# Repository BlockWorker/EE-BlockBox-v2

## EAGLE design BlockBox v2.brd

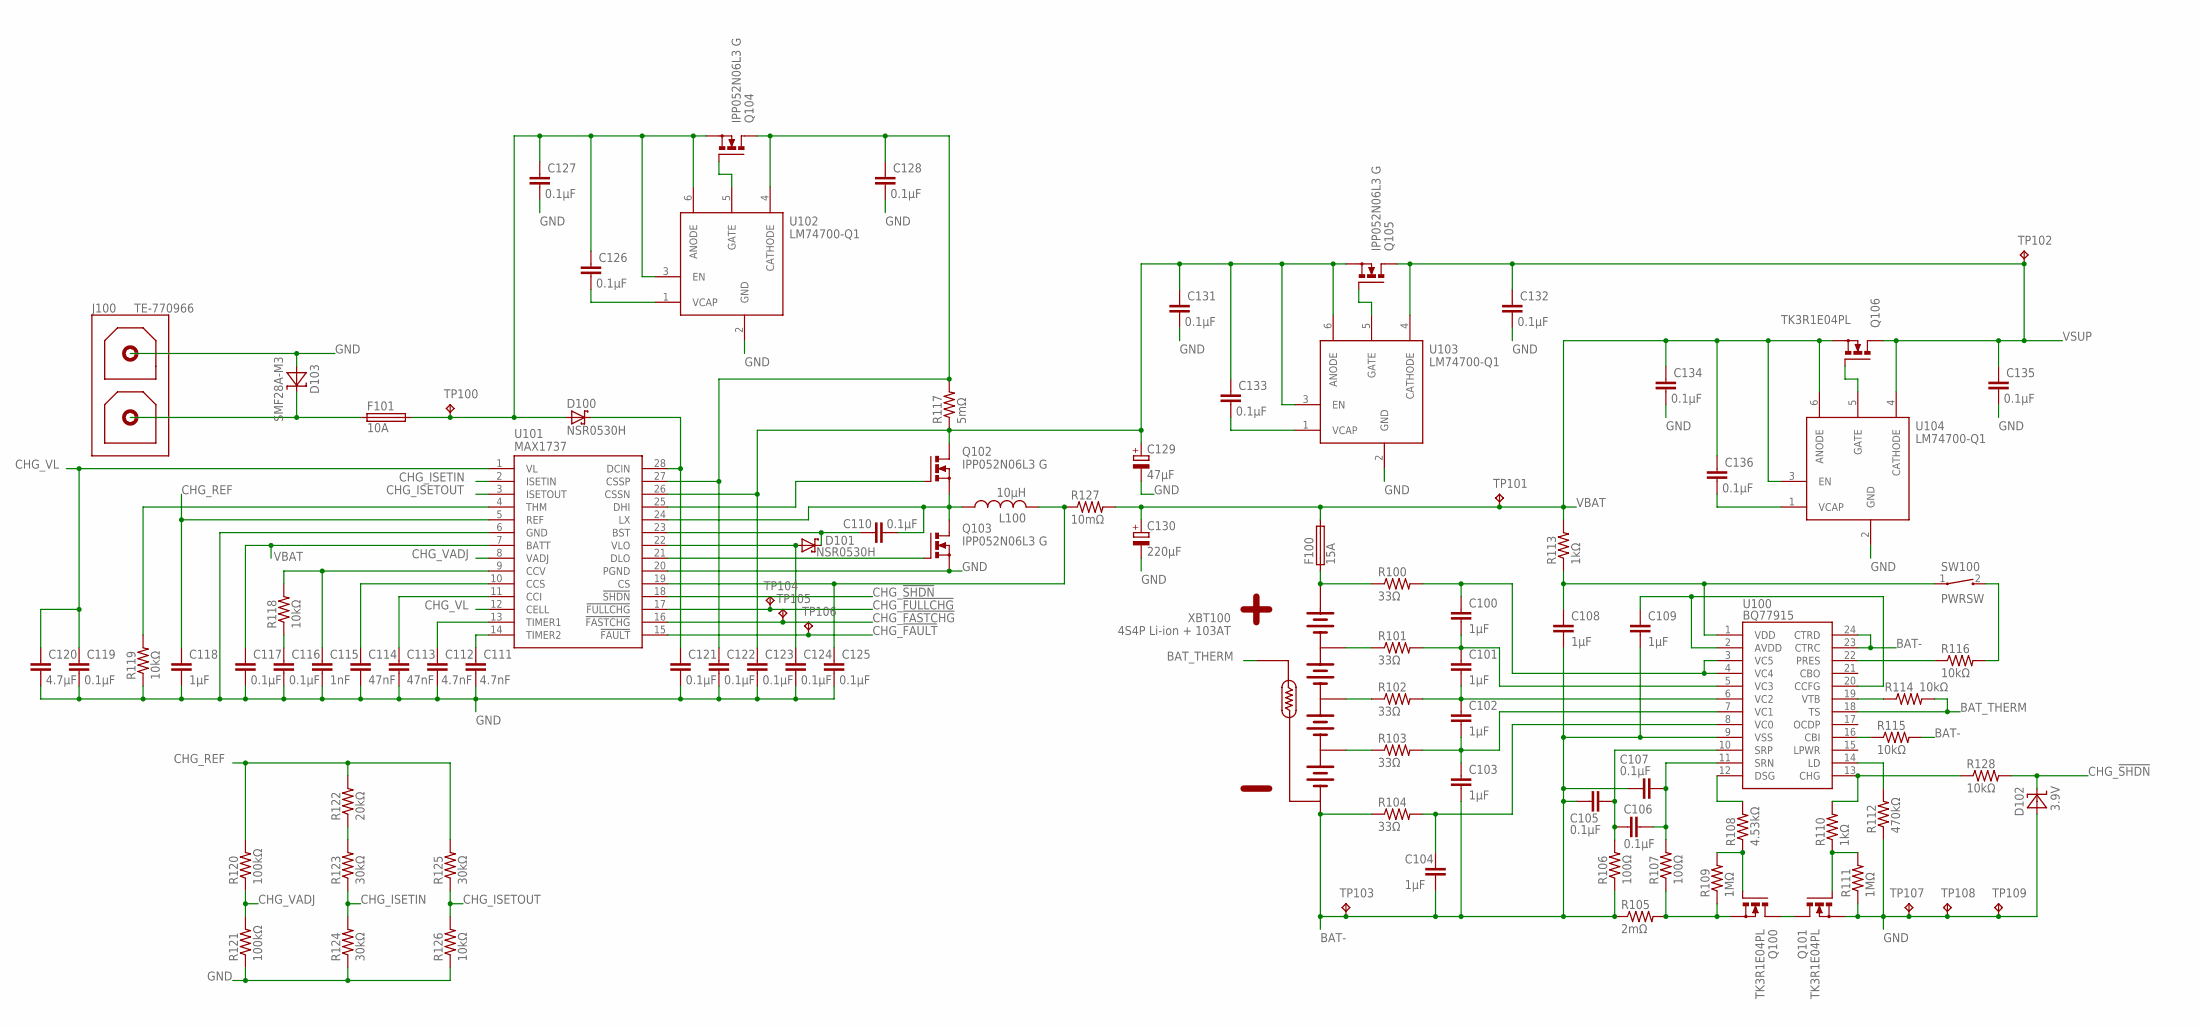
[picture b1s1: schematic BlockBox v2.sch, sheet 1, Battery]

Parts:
C100, C101, C102, C103, C104, C108, C109, C118: 1µF; C0603
C105, C106, C107, C110, C116, C117, C119, C121, C122, C123, C124, C125, C126, C127, C128, C131, C132, C133, C134, C135, C136: 0.1µF; C0603
C111, C112: 4.7nF; C0603
C113, C114: 47nF; C0603
C115: 1nF; C0603
C120: 4.7µF; C0805
C129: 47µF; E2,5-6
C130: 220µF; E3,5-8
D100, D101: NSR0530H; SOD323
D102: 3.9V; SOD323
D103: SMF28A-M3; DO-219AB
F100: 15A; F2410
F101: 10A; F2410
J100: TE-770966
L100: 10µH; PM5022
Q100, Q101, Q106: TK3R1E04PL; TO220BV-HS1
Q102, Q103, Q104, Q105: IPP052N06L3 G; TO220BV-HS1
R100, R101, R102, R103, R104: 33Ω; R0603
R105: 2mΩ; R2512
R106, R107: 100Ω; R0603
R108: 4.53kΩ; R0603
R109, R111: 1MΩ; R0603
R110, R113: 1kΩ; R0603
R112: 470kΩ; R0603
R114, R115, R116, R118, R119, R126, R128: 10kΩ; R0603
R117: 5mΩ; R1206
R120, R121: 100kΩ; R0603
R122: 20kΩ; R0603
R123, R124, R125: 30kΩ; R0603
R127: 10mΩ; R1206
SW100: PWRSW; WIRE-2P-SIMPLE
TP100, TP101, TP102, TP103, TP104, TP105, TP106, TP107, TP108, TP109: TPTP15R; TP15R
U100: BQ77915; TSSOP24
U101: MAX1737; QSOP28
U102, U103, U104: LM74700-Q1; SOT23-6L
XBT100: 4S4P Li-ion + 103AT; TE-770970

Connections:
BAT-: C103.2, C104.2, C105.1, C107.1, C108.2, C109.2, R104.1, R105.1, R106.1, R115.2, TP103.TP, U100.9 (VSS), U100.23 (CTRC), U100.24 (CTRD), XBT100.5 (-), XBT100.6 (-); also elsewhere on the board
BAT-_INT1: Q100.S, R105.2, R107.1, R109.1
BAT-_INT2: Q100.D, Q101.D
BAT_AVDD: C109.1, U100.2 (AVDD), U100.20 (CCFG)
BAT_BAL0: C104.1, R104.2, U100.8 (VC0)
BAT_BAL1: C102.2, C103.1, R103.2, U100.7 (VC1)
BAT_BAL2: C101.2, C102.1, R102.2, U100.6 (VC2)
BAT_BAL3: C100.2, C101.1, R101.2, U100.5 (VC3)
BAT_BAL4: C100.1, R100.2, U100.3 (VC5), U100.4 (VC4)
BAT_CBI: R115.1, U100.16 (CBI)
BAT_CHG_CTL: R110.2, R128.1, U100.13 (CHG)
BAT_CHG_GATE: Q101.G, R110.1, R111.2
BAT_CSN: C106.2, C107.2, R107.2, U100.11 (SRN); also elsewhere on the board
BAT_CSP: C105.2, C106.1, R106.2, U100.10 (SRP); also elsewhere on the board
BAT_DSG_CTL: R108.2, U100.12 (DSG)
BAT_DSG_GATE: Q100.G, R108.1, R109.2
BAT_INT1: R103.1, XBT100.4 (BAL1)
BAT_INT2: R102.1, XBT100.3 (BAL2)
BAT_INT3: R101.1, XBT100.7 (BAL3)
BAT_LD: R112.2, U100.14 (LD)
BAT_PRES: R116.1, U100.22 (PRES)
BAT_PRES_SW: R116.2, SW100.2
BAT_THERM: R114.2, U100.18 (TS), XBT100.8 (THERM1)
BAT_VDD: C108.1, R113.1, SW100.1, U100.1 (VDD)
BAT_VTB: R114.1, U100.19 (VTB)
CHG_!FASTCHG: TP105.TP, U101.16 (!FASTCHG); also elsewhere on the board
CHG_!FAULT: TP106.TP, U101.15 (!FAULT); also elsewhere on the board
CHG_!FULLCHG: TP104.TP, U101.17 (!FULLCHG); also elsewhere on the board
CHG_!SHDN: D102.1 (C), R128.2, U101.18 (!SHDN)
CHG_BST: C110.1, D101.1 (C), U101.23 (BST)
CHG_CCI: C113.1, U101.11 (CCI)
CHG_CCS: C114.1, U101.10 (CCS)
CHG_CCV: C115.1, R118.2, U101.9 (CCV)
CHG_CCV_FILT: C116.1, R118.1
CHG_CS: C125.1, L100.2, R127.1, U101.19 (CS)
CHG_CSSN: C123.1, C129.+, C131.1, C133.1, Q102.D, Q105.S, R117.1, U101.26 (CSSN), U103.3 (EN), U103.6 (ANODE)
CHG_CSSP: C122.1, C128.1, Q104.D, R117.2, U101.27 (CSSP), U102.4 (CATHODE)
CHG_DCIN: C121.1, D100.1 (C), U101.28 (DCIN)
CHG_DHI: Q102.G, U101.25 (DHI)
CHG_DLO: Q103.G, U101.21 (DLO)
CHG_ISETIN: R123.1, R124.2, U101.2 (ISETIN)
CHG_ISETIN_INT: R122.1, R123.2
CHG_ISETOUT: R125.1, R126.2, U101.3 (ISETOUT)
CHG_LX: C110.2, L100.1, Q102.S, Q103.D, U101.24 (LX)
CHG_REF: C118.1, R120.2, R122.2, R125.2, U101.5 (REF)
CHG_THM: R119.2, U101.4 (THM)
CHG_TIMER1: C112.1, U101.13 (TIMER1)
CHG_TIMER2: C111.1, U101.14 (TIMER2)
CHG_VADJ: R120.1, R121.2, U101.8 (VADJ)
CHG_VL: C119.1, C120.1, U101.1 (VL), U101.12 (CELL)
CHG_VLO: C124.1, D101.2 (A), U101.22 (VLO)
GND: C111.2, C112.2, C113.2, C114.2, C115.2, C116.2, C117.2, C118.2, C119.2, C120.2, C121.2, C122.2, C123.2, C124.2, C125.2, C127.2, C128.2, C129.-, C130.-, C131.2, C132.2, C134.2, C135.2, D102.2 (A), D103.A, J100.2, Q101.S, Q103.S, R111.1, R112.1, R119.1, R121.1, R124.1, R126.1, TP107.TP, TP108.TP, TP109.TP, U101.6 (GND), U101.20 (PGND), U102.2 (GND), U103.2 (GND), U104.2 (GND); also elsewhere on the board
VBAT: C117.1, C130.+, C134.1, C136.1, F100.2, Q106.S, R113.2, R127.2, TP101.TP, U101.7 (BATT), U104.3 (EN), U104.6 (ANODE); also elsewhere on the board
VBAT_PREFUSE: F100.1, R100.1, XBT100.1 (+), XBT100.2 (+)
VIN_EXT: D103.K (C), F101.1, J100.1
VIN_EXT_FUSED: C126.1, C127.1, D100.2 (A), F101.2, Q104.S, TP100.TP, U102.3 (EN), U102.6 (ANODE)
VIN_ID_GATE: Q104.G, U102.5 (GATE)
VIN_ID_VCAP: C126.2, U102.1 (VCAP)
VSUP: C132.1, C135.1, Q105.D, Q106.D, TP102.TP, U103.4 (CATHODE), U104.4 (CATHODE); also elsewhere on the board
VSUP_ID1_GATE: Q105.G, U103.5 (GATE)
VSUP_ID1_VCAP: C133.2, U103.1 (VCAP)
VSUP_ID2_GATE: Q106.G, U104.5 (GATE)
VSUP_ID2_VCAP: C136.2, U104.1 (VCAP)

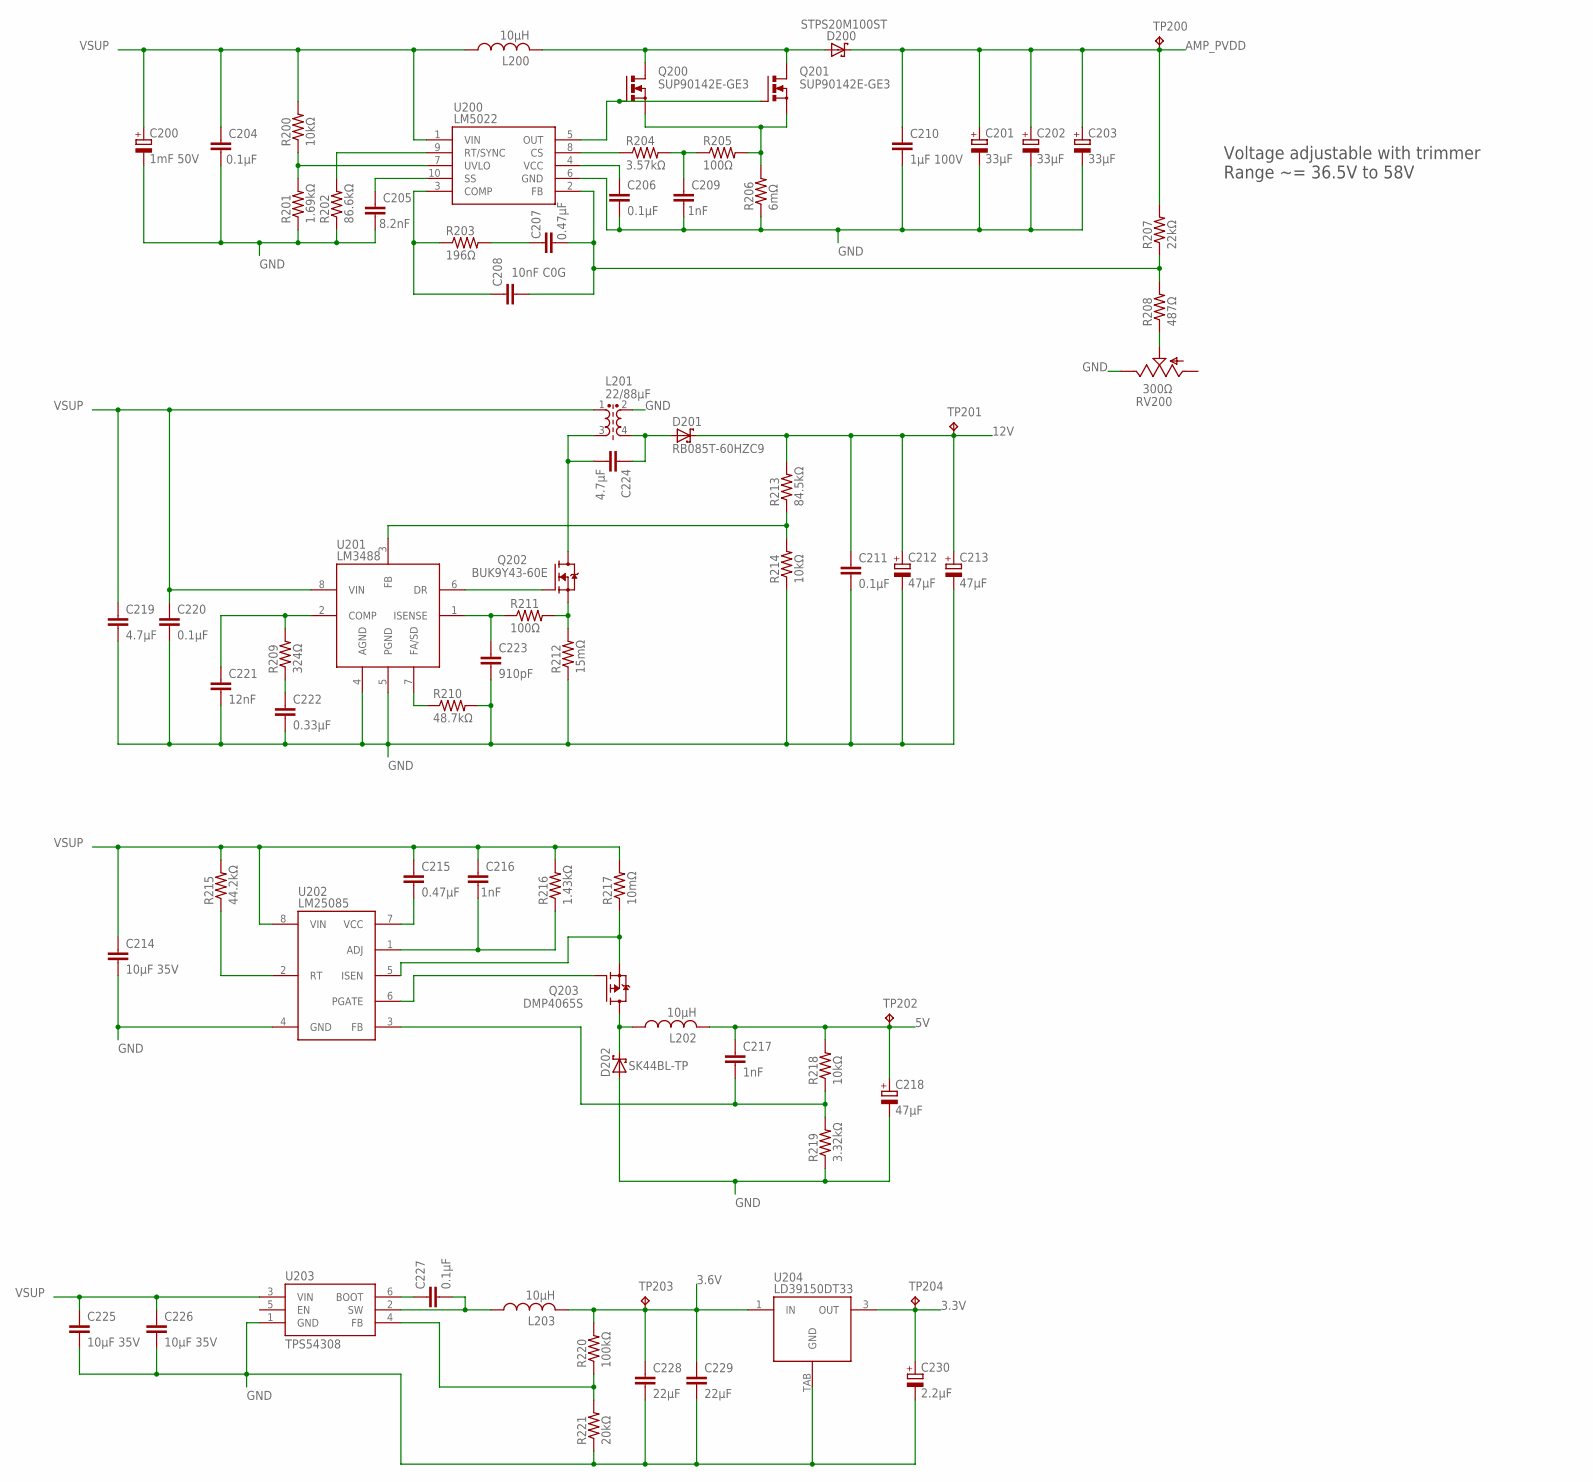
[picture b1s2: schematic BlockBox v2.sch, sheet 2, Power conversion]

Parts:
C200: 1mF 50V; E7,5-16
C201, C202, C203: 33µF; E3,5-8
C204, C206, C211, C220, C227: 0.1µF; C0603
C205: 8.2nF; C0603
C207: 0.47µF; C050-035X075
C208: 10nF C0G; C0603
C209, C216, C217: 1nF; C0603
C210: 1µF 100V; C1206
C212, C213, C218: 47µF; E2,5-6
C214, C225, C226: 10µF 35V; C1206
C215: 0.47µF; C0603
C219, C224: 4.7µF; C0805
C221: 12nF; C0603
C222: 0.33µF; C050-035X075
C223: 910pF; C0603
C228, C229: 22µF; C0805
C230: 2.2µF; PANASONIC_B
D200: STPS20M100ST; TO220ABS-HS1
D201: RB085T-60HZC9; TO220ABS-HS1
D202: SK44BL-TP; DO-214AA
L200: 10µH; PQ2614B
L201: 22/88µF; SRF1280A
L202: 10µH; SRN1060
L203: 10µH; RLB0912
Q200, Q201: SUP90142E-GE3; TO220BV-HS1
Q202: BUK9Y43-60E; SOT669
Q203: DMP4065S; SOT23
R200, R214, R218: 10kΩ; R0603
R201: 1.69kΩ; R0603
R202: 86.6kΩ; R0603
R203: 196Ω; R0603
R204: 3.57kΩ; R0603
R205, R211: 100Ω; R0603
R206: 6mΩ; R2512
R207: 22kΩ; R0603
R208: 487Ω; R0603
R209: 324Ω; R0603
R210: 48.7kΩ; R0603
R212: 15mΩ; R0612
R213: 84.5kΩ; R0603
R215: 44.2kΩ; R0603
R216: 1.43kΩ; R0603
R217: 10mΩ; R1206
R219: 3.32kΩ; R0603
R220: 100kΩ; R0603
R221: 20kΩ; R0603
RV200: 300Ω; TC33X-2
TP200, TP201, TP202, TP203, TP204: TPTP15R; TP15R
U200: LM5022; VSSOP10
U201: LM3488; VSSOP8
U202: LM25085; VSSOP8
U203: TPS54308; SOT23-6L
U204: LD39150DT33; DPAK

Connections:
3.3V: C230.+, TP204.TP, U204.3 (OUT); also elsewhere on the board
3.6V: C228.1, C229.1, L203.2, R220.2, TP203.TP, U204.1 (IN)
5V: C217.1, C218.+, L202.2, R218.2, TP202.TP; also elsewhere on the board
12V: C211.1, C212.+, C213.+, D201.C, R213.2, TP201.TP; also elsewhere on the board
AMP_PVDD: C201.+, C202.+, C203.+, C210.1, D200.C, R207.2, TP200.TP; also elsewhere on the board
BOOST_COMP: C208.1, R203.1, U200.3 (COMP)
BOOST_COMP_INT: C207.1, R203.2
BOOST_CS: R204.1, U200.8 (CS)
BOOST_CS_FILTER: C209.1, R204.2, R205.1
BOOST_FB: C207.2, C208.2, R207.1, R208.2, U200.2 (FB)
BOOST_FB_ADJ: R208.1, RV200.2 (S)
BOOST_RT: R202.2, U200.9 (RT/SYNC)
BOOST_SS: C205.1, U200.10 (SS)
BOOST_SW_DRAIN: D200.A1 (A), D200.A2 (A), L200.2, Q200.D, Q201.D
BOOST_SW_GATE: Q200.G, Q201.G, U200.5 (OUT)
BOOST_SW_SOURCE: Q200.S, Q201.S, R205.2, R206.2
BOOST_UVLO: R200.1, R201.2, U200.7 (UVLO)
BOOST_VCC: C206.1, U200.4 (VCC)
BUCK_ADJ: C216.2, R216.1, U202.1 (ADJ)
BUCK_FB: C217.2, R218.1, R219.2, U202.3 (FB)
BUCK_RT: R215.1, U202.2 (RT)
BUCK_SW_DRAIN: Q203.2 (S), R217.1, U202.5 (ISEN)
BUCK_SW_GATE: Q203.1 (G), U202.6 (PGATE)
BUCK_SW_SOURCE: D202.K (C), L202.1, Q203.3 (D)
BUCK_VCC: C215.2, U202.7 (VCC)
GND: C200.-, C201.-, C202.-, C203.-, C204.2, C205.2, C206.2, C209.2, C210.2, C211.2, C212.-, C213.-, C214.2, C218.-, C219.2, C220.2, C221.2, C222.2, C223.2, C225.2, C226.2, C228.2, C229.2, C230.-, D202.A, L201.2 (S1), R201.1, R202.1, R206.1, R210.2, R212.1, R214.1, R219.1, R221.1, RV200.3 (E), U200.6 (GND), U201.4 (AGND), U201.5 (PGND), U202.4 (GND), U203.1 (GND), U204.TAB (GND); also elsewhere on the board
PRELIN_BOOT: C227.1, U203.6 (BOOT)
PRELIN_FB: R220.1, R221.2, U203.4 (FB)
PRELIN_SW: C227.2, L203.1, U203.2 (SW)
SEPIC_COMP: C221.1, R209.2, U201.2 (COMP)
SEPIC_COMP_INT: C222.1, R209.1
SEPIC_FA: R210.1, U201.7 (FA/SD)
SEPIC_FB: R213.1, R214.2, U201.3 (FB)
SEPIC_ISENSE: C223.1, R211.1, U201.1 (ISENSE)
SEPIC_PREDIODE: C224.1, D201.A1 (A), D201.A2 (A), L201.4 (S2)
SEPIC_SW_DRAIN: C224.2, L201.3 (P2), Q202.MB (D)
SEPIC_SW_GATE: Q202.4 (G), U201.6 (DR)
SEPIC_SW_SOURCE: Q202.1 (S), Q202.2 (S), Q202.3 (S), R211.2, R212.2
VSUP: C200.+, C204.1, C214.1, C215.1, C216.1, C219.1, C220.1, C225.1, C226.1, L200.1, L201.1, R200.2, R215.2, R216.2, R217.2, U200.1 (VIN), U201.8 (VIN), U202.8 (VIN), U203.3 (VIN); also elsewhere on the board

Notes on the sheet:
Voltage adjustable with trimmer Range ~= 36.5V to 58V

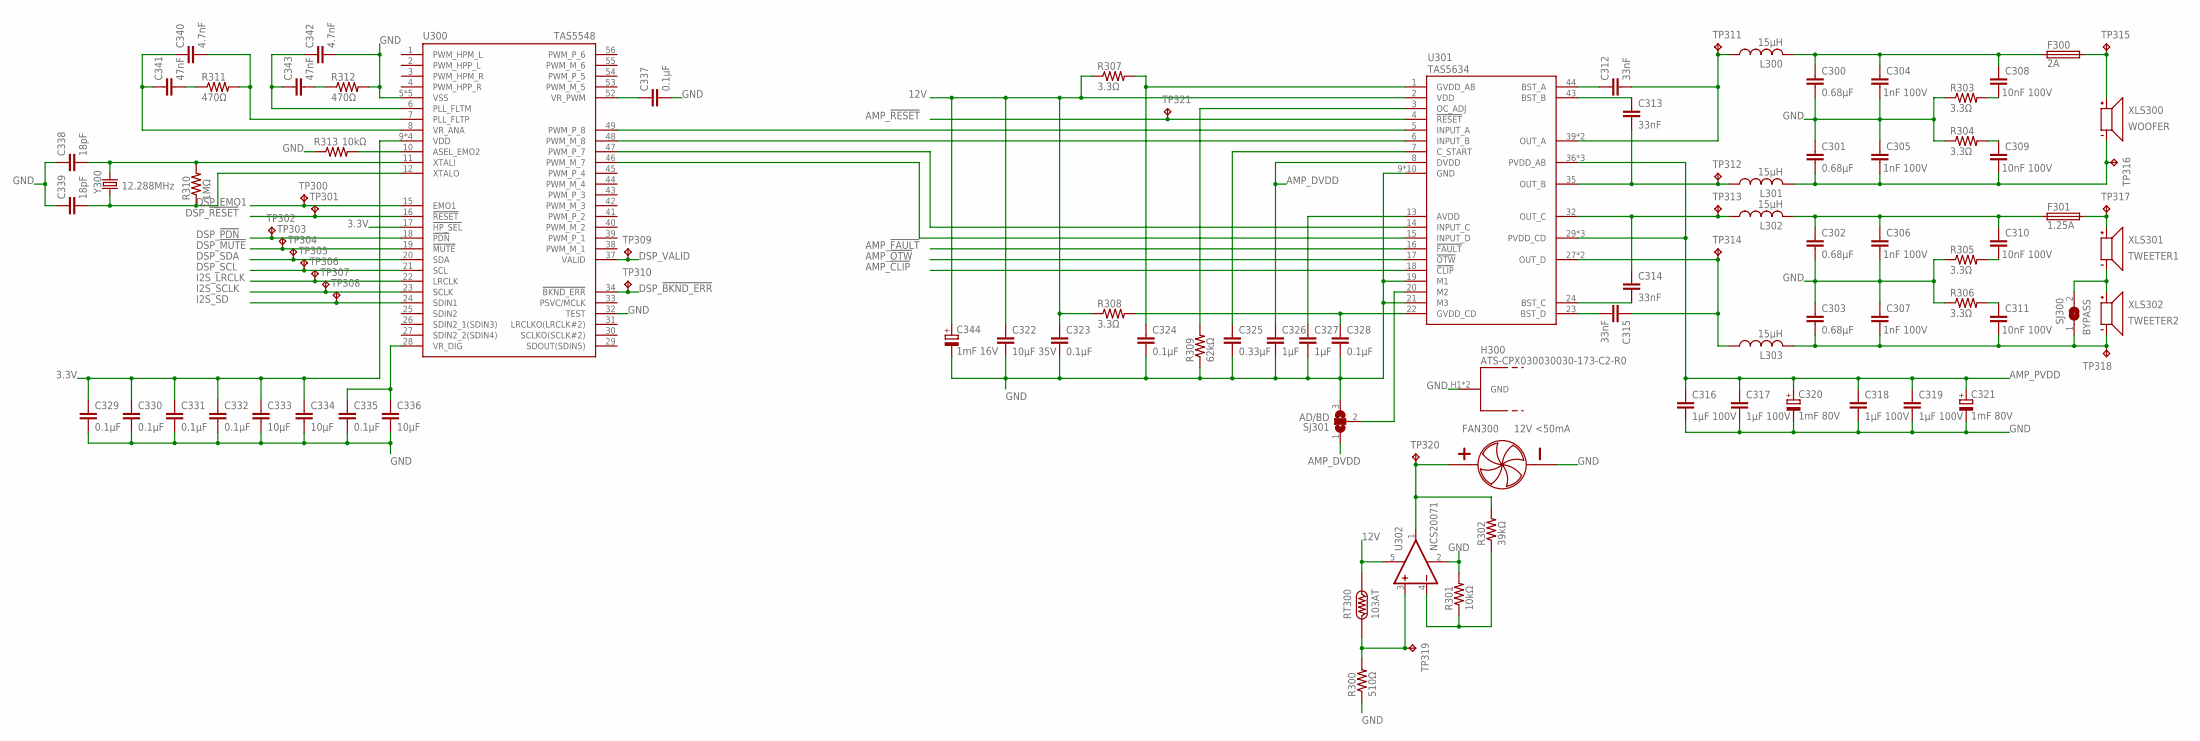
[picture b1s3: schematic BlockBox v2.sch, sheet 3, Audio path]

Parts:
C300, C301, C302, C303: 0.68µF; C150-064X183
C304, C305, C306, C307: 1nF 100V; C0603
C308, C309, C310, C311: 10nF 100V; C0603
C312, C313, C314, C315: 33nF; C0805
C316, C317, C318, C319: 1µF 100V; C1206
C320, C321: 1mF 80V; E7,5-16
C322: 10µF 35V; C1206
C323, C324, C328, C329, C330, C331, C332, C335, C337: 0.1µF; C0603
C325: 0.33µF; C0603
C326, C327: 1µF; C0603
C333, C334, C336: 10µF; C0805
C338, C339: 18pF; C0603
C340, C342: 4.7nF; C0603
C341, C343: 47nF; C0603
C344: 1mF 16V; E5-10,5
F300: 2A; MRF_FUSE
F301: 1.25A; MRF_FUSE
FAN300: 12V <50mA; WIRE-2P-SIMPLE
H300: ATS-CPX030030030-173-C2-R0
L300, L301, L302, L303: 15µH; 1D14A
R300: 510Ω; R0603
R301, R313: 10kΩ; R0603
R302: 39kΩ; R0603
R303, R304, R305, R306, R307, R308: 3.3Ω; R0805
R309: 62kΩ; R0603
R310: 1MΩ; R0603
R311, R312: 470Ω; R0603
RT300: 103AT; WIRE-2P-SIMPLE
SJ300: BYPASS; SJ
SJ301: AD/BD; SJ_2
TP300, TP301, TP302, TP303, TP304, TP305, TP306, TP307, TP308, TP309, TP310, TP311, TP312, TP313, TP314, TP315, TP316, TP317, TP318, TP319, TP320, TP321: TPTP15R; TP15R
U300: TAS5548; HTSSOP56DCA
U301: TAS5634; TSSOP44
U302: NCS20071; TSOP-5
XLS300: WOOFER; TE-770966
XLS301: TWEETER1; TE-770966
XLS302: TWEETER2; TE-770966
Y300: 12.288MHz; HC49US

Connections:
3.3V: C329.1, C330.1, C331.1, C332.1, C333.1, C334.1, U300.9 (VDD), U300.14 (VDD), U300.17 (!HP_SEL), U300.35 (VDD), U300.50 (VDD); also elsewhere on the board
12V: C322.1, C323.1, C344.+, R307.1, R308.1, RT300.1, U301.2 (VDD), U302.5 (V+); also elsewhere on the board
AMP_!CLIP: U301.18 (!CLIP); also elsewhere on the board
AMP_!FAULT: U301.16 (!FAULT); also elsewhere on the board
AMP_!OTW: U301.17 (!OTW); also elsewhere on the board
AMP_!RESET: TP321.TP, U301.4 (!RESET); also elsewhere on the board
AMP_AVDD: C327.1, U301.13 (AVDD)
AMP_A_FILT: C300.1, C304.1, C308.1, F300.1, L300.2
AMP_A_FILT_INT: C308.2, R303.2
AMP_A_FUSED: F300.2, TP315.TP, XLS300.2 (+)
AMP_BST_A: C312.1, U301.44 (BST_A)
AMP_BST_B: C313.1, U301.43 (BST_B)
AMP_BST_C: C314.2, U301.24 (BST_C)
AMP_BST_D: C315.2, U301.23 (BST_D)
AMP_B_FILT: C301.1, C305.2, C309.2, L301.2, TP316.TP, XLS300.1 (-)
AMP_B_FILT_INT: C309.1, R304.2
AMP_CD_MID: SJ300.2, XLS301.1 (-), XLS302.2 (+)
AMP_C_FILT: C302.1, C306.1, C310.1, F301.1, L302.2
AMP_C_FILT_INT: C310.2, R305.2
AMP_C_FUSED: F301.2, TP317.TP, XLS301.2 (+)
AMP_C_START: C325.1, U301.7 (C_START)
AMP_DVDD: C326.1, SJ301.1, U301.8 (DVDD)
AMP_D_FILT: C303.1, C307.2, C311.2, L303.2, SJ300.1, TP318.TP, XLS302.1 (-)
AMP_D_FILT_INT: C311.1, R306.2
AMP_FAN_+: FAN300.1 (+), R302.2, TP320.TP, U302.1 (OUT)
AMP_FAN_FB: R301.1, R302.1, U302.4 (-IN)
AMP_FAN_SENSE: R300.2, RT300.2, TP319.TP, U302.3 (+IN)
AMP_GVDD_AB: C324.1, R307.2, U301.1 (GVDD_AB)
AMP_GVDD_CD: C328.1, R308.2, U301.22 (GVDD_CD)
AMP_INPUT_A: U300.49 (PWM_P_8), U301.5 (INPUT_A)
AMP_INPUT_B: U300.48 (PWM_M_8), U301.6 (INPUT_B)
AMP_INPUT_C: U300.47 (PWM_P_7), U301.14 (INPUT_C)
AMP_INPUT_D: U300.46 (PWM_M_7), U301.15 (INPUT_D)
AMP_M2: SJ301.2, U301.20 (M2)
AMP_OC_ADJ: R309.2, U301.3 (OC_ADJ)
AMP_OUT_A: C312.2, L300.1, TP311.TP, U301.39 (OUT_A), U301.40 (OUT_A)
AMP_OUT_B: C313.2, L301.1, TP312.TP, U301.35 (OUT_B)
AMP_OUT_C: C314.1, L302.1, TP313.TP, U301.32 (OUT_C)
AMP_OUT_D: C315.1, L303.1, TP314.TP, U301.27 (OUT_D), U301.28 (OUT_D)
AMP_PVDD: C316.1, C317.1, C318.1, C319.1, C320.+, C321.+, U301.29 (PVDD_CD), U301.30 (PVDD_CD), U301.31 (PVDD_CD), U301.36 (PVDD_AB), U301.37 (PVDD_AB), U301.38 (PVDD_AB); also elsewhere on the board
DSP_!BKND_ERR: TP310.TP, U300.34 (!BKND_ERR); also elsewhere on the board
DSP_!MUTE: TP303.TP, U300.19 (!MUTE); also elsewhere on the board
DSP_!PDN: TP302.TP, U300.18 (!PDN); also elsewhere on the board
DSP_!RESET: TP301.TP, U300.16 (!RESET); also elsewhere on the board
DSP_ASEL_EMO2: R313.2, U300.10 (ASEL_EMO2)
DSP_EMO1: TP300.TP, U300.15 (EMO1); also elsewhere on the board
DSP_PLL_FLTM: C342.1, C343.1, U300.6 (PLL_FLTM)
DSP_PLL_FLTP: C340.2, R311.2, U300.7 (PLL_FLTP)
DSP_PLL_FLTP_INT: C341.2, R311.1
DSP_PLL_FPLM_INT: C343.2, R312.1
DSP_SCL: TP305.TP, U300.21 (SCL); also elsewhere on the board
DSP_SDA: TP304.TP, U300.20 (SDA); also elsewhere on the board
DSP_VALID: TP309.TP, U300.37 (VALID); also elsewhere on the board
DSP_VR_ANA: C340.1, C341.1, U300.8 (VR_ANA)
DSP_VR_DIG: C335.1, C336.1, U300.28 (VR_DIG)
DSP_VR_PWM: C337.1, U300.52 (VR_PWM)
DSP_XTALI: C338.2, R310.2, U300.11 (XTALI), Y300.2
DSP_XTALO: C339.2, R310.1, U300.12 (XTALO), Y300.1
GND: C300.2, C301.2, C302.2, C303.2, C304.2, C305.1, C306.2, C307.1, C316.2, C317.2, C318.2, C319.2, C320.-, C321.-, C322.2, C323.2, C324.2, C325.2, C326.2, C327.2, C328.2, C329.2, C330.2, C331.2, C332.2, C333.2, C334.2, C335.2, C336.2, C337.2, C338.1, C339.1, C342.2, C344.-, FAN300.2 (-), H300.H1, H300.H2, R300.1, R301.2, R303.1, R304.1, R305.1, R306.1, R309.1, R312.2, R313.1, SJ301.3, U300.5 (VSS), U300.13 (VSS), U300.32 (TEST), U300.36 (VSS), U300.51 (VSS), U300.EXP (VSS), U301.9 (GND), U301.10 (GND), U301.11 (GND), U301.12 (GND), U301.19 (M1), U301.21 (M3), U301.25 (GND), U301.26 (GND), U301.33 (GND), U301.34 (GND), U301.41 (GND), U301.42 (GND), U302.2 (V-); also elsewhere on the board
I2S_LRCLK: TP306.TP, U300.22 (LRCLK); also elsewhere on the board
I2S_SCLK: TP307.TP, U300.23 (SCLK); also elsewhere on the board
I2S_SD: TP308.TP, U300.24 (SDIN1); also elsewhere on the board

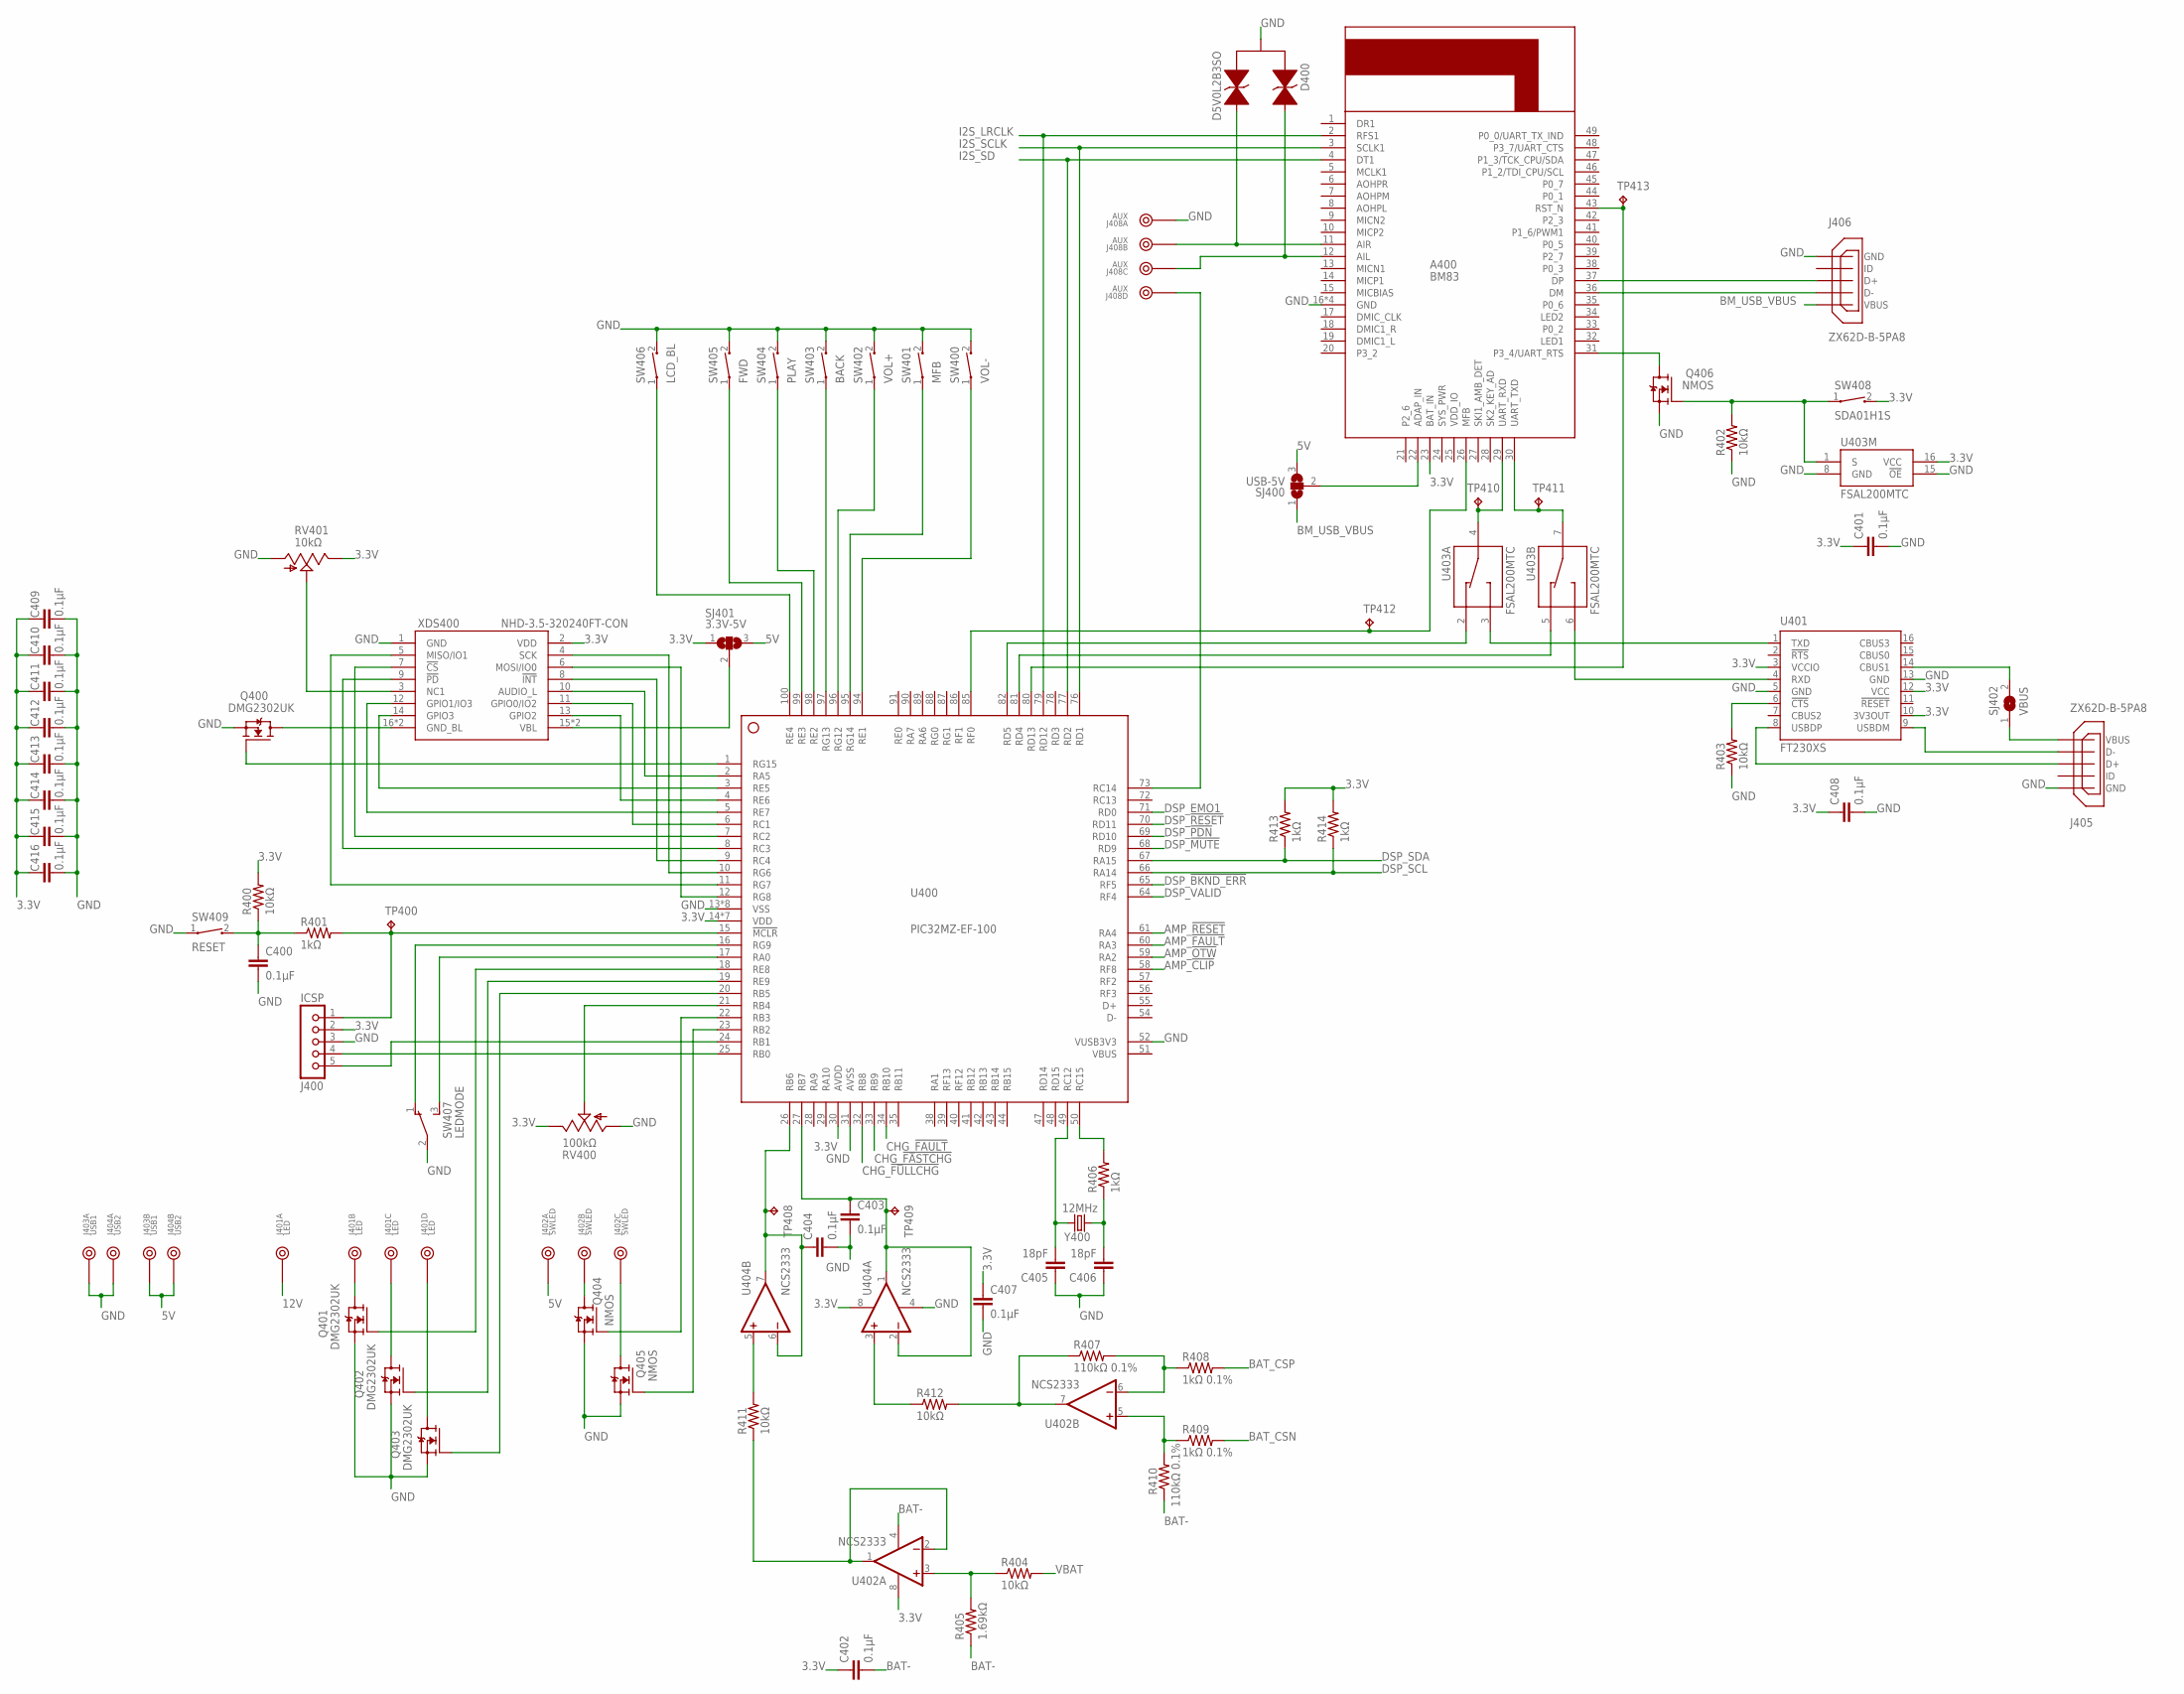
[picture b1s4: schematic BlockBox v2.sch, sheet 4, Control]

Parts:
A400: BM83
C400, C401, C402, C403, C404, C407, C408, C409, C410, C411, C412, C413, C414, C415, C416: 0.1µF; C0603
C405, C406: 18pF; C0603
D400: D5V0L2B3SO; SOT23
J400: ICSP; 5P-1.27-POGO
J401: LED; 4PIN
J402: SWLED; 3PIN
J403: USB1; 2PIN
J404: USB2; 2PIN
J405, J406: ZX62D-B-5PA8
J408: AUX; 4PIN
Q400, Q401, Q402, Q403: DMG2302UK; SOT23
Q404, Q405, Q406: NMOS; SOT23
R400, R402, R403, R404, R411, R412: 10kΩ; R0603
R401, R406, R413, R414: 1kΩ; R0603
R405: 1.69kΩ; R0603
R407, R410: 110kΩ 0.1%; R0603
R408, R409: 1kΩ 0.1%; R0603
RV400: 100kΩ; WIRE-3P-SIMPLE
RV401: 10kΩ; TC33X-2
SJ400: USB-5V; SJ_2
SJ401: 3.3V-5V; SJ_2
SJ402: VBUS; SJ
SW400: VOL-; WIRE-2P-SIMPLE
SW401: MFB; WIRE-2P-SIMPLE
SW402: VOL+; WIRE-2P-SIMPLE
SW403: BACK; WIRE-2P-SIMPLE
SW404: PLAY; WIRE-2P-SIMPLE
SW405: FWD; WIRE-2P-SIMPLE
SW406: LCD_BL; WIRE-2P-SIMPLE
SW407: LEDMODE; WIRE-3P-SIMPLE
SW408: SDA01H1S
SW409: RESET; WIRE-2P-SIMPLE
TP400, TP408, TP409, TP410, TP411, TP412, TP413: TPTP15R; TP15R
U400: PIC32MZ-EF-100; TQFP100-14X14X1MM
U401: FT230XS; SSOP16
U402, U404: NCS2333; MSOP8
U403: FSAL200MTC; TSSOP16L
XDS400: NHD-3.5-320240FT-CON; 2X9PIN
Y400: 12MHz; HC49US

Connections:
3.3V: A400.23 (BAT_IN), C401.1, C402.1, C407.1, C408.1, C409.1, C410.1, C411.1, C412.1, C413.1, C414.1, C415.1, C416.1, J400.2, R400.2, R413.2, R414.2, RV400.3 (E), RV401.3 (E), SJ401.1, SW408.2, U400.14 (VDD), U400.30 (AVDD), U400.37 (VDD), U400.46 (VDD), U400.62 (VDD), U400.74 (VDD), U400.83 (VDD), U400.93 (VDD), U401.3 (VCCIO), U401.10 (3V3OUT), U401.12 (VCC), U402.8 (V+), U403.16 (VCC), U404.8 (V+), XDS400.2 (VDD); also elsewhere on the board
5V: J402.1, J403.2, J404.2, SJ400.3, SJ401.3; also elsewhere on the board
12V: J401.1; also elsewhere on the board
AMP_!CLIP: U400.58 (RF8); also elsewhere on the board
AMP_!FAULT: U400.60 (RA3); also elsewhere on the board
AMP_!OTW: U400.59 (RA2); also elsewhere on the board
AMP_!RESET: U400.61 (RA4); also elsewhere on the board
BAT-: C402.2, R405.1, R410.1, U402.4 (V-); also elsewhere on the board
BAT_CSN: R409.2; also elsewhere on the board
BAT_CSP: R408.2; also elsewhere on the board
BM_!RST: A400.43 (RST_N), TP413.TP, U400.80 (RD13)
BM_ADAP_IN: A400.22 (ADAP_IN), SJ400.2
BM_AUX_L: A400.12 (AIL), D400.1, J408.3
BM_AUX_R: A400.11 (AIR), D400.2, J408.2
BM_MFB: A400.26 (MFB), TP412.TP, U400.85 (RF0)
BM_P3_4: A400.31 (P3_4/UART_RTS), Q406.3 (D)
BM_UART_RXD: A400.29 (UART_RXD), TP410.TP, U403.4 (A)
BM_UART_SWITCH: Q406.1 (G), R402.2, SW408.1, U403.1 (S)
BM_UART_TXD: A400.30 (UART_TXD), TP411.TP, U403.7 (A)
BM_USB_D+: A400.37 (DP), J406.3 (D+)
BM_USB_D-: A400.36 (DM), J406.2 (D-)
BM_USB_VBUS: J406.1 (VBUS), SJ400.1
CHG_!FASTCHG: U400.33 (RB9); also elsewhere on the board
CHG_!FAULT: U400.34 (RB10); also elsewhere on the board
CHG_!FULLCHG: U400.32 (RB8); also elsewhere on the board
DSP_!BKND_ERR: U400.65 (RF5); also elsewhere on the board
DSP_!MUTE: U400.68 (RD9); also elsewhere on the board
DSP_!PDN: U400.69 (RD10); also elsewhere on the board
DSP_!RESET: U400.70 (RD11); also elsewhere on the board
DSP_EMO1: U400.71 (RD0); also elsewhere on the board
DSP_SCL: R414.1, U400.66 (RA14); also elsewhere on the board
DSP_SDA: R413.1, U400.67 (RA15); also elsewhere on the board
DSP_VALID: U400.64 (RF4); also elsewhere on the board
FT_!CTS: R403.2, U401.6 (!CTS)
FT_RXD: U401.4 (RXD), U403.6 (B2)
FT_TXD: U401.1 (TXD), U403.3 (B2)
FT_USB_D+: J405.3 (D+), U401.8 (USBDP)
FT_USB_D-: J405.2 (D-), U401.9 (USBDM)
FT_USB_VBUS: J405.1 (VBUS), SJ402.1
FT_VBUS_SENSE: SJ402.2, U401.14 (CBUS1)
GND: A400.16 (GND), A400.50 (GND), A400.G1 (GND), A400.G2 (GND), C400.2, C401.2, C403.2, C404.2, C405.1, C406.1, C407.2, C408.2, C409.2, C410.2, C411.2, C412.2, C413.2, C414.2, C415.2, C416.2, D400.3 (C), J400.3, J403.1, J404.1, J405.5 (GND), J405.S1 (GND), J405.S2 (GND), J405.S3 (GND), J405.S4 (GND), J406.5 (GND), J406.S1 (GND), J406.S2 (GND), J406.S3 (GND), J406.S4 (GND), J408.1, Q400.2 (S), Q401.2 (S), Q402.2 (S), Q403.2 (S), Q404.2 (S), Q405.2 (S), Q406.2 (S), R402.1, R403.1, RV400.1 (A), RV401.1 (A), SW400.2, SW401.2, SW402.2, SW403.2, SW404.2, SW405.2, SW406.2, SW407.2, SW409.1, U400.13 (VSS), U400.31 (AVSS), U400.36 (VSS), U400.45 (VSS), U400.52 (VUSB3V3), U400.53 (VSS), U400.63 (VSS), U400.75 (VSS), U400.84 (VSS), U400.92 (VSS), U401.5 (GND), U401.13 (GND), U403.8 (GND), U403.15 (!OE), U404.4 (V-), XDS400.1 (GND); also elsewhere on the board
I2S_LRCLK: A400.2 (RFS1), U400.79 (RD12); also elsewhere on the board
I2S_SCLK: A400.3 (SCLK1), U400.76 (RD1); also elsewhere on the board
I2S_SD: A400.4 (DT1), U400.77 (RD2); also elsewhere on the board
LCD_!CS: U400.7 (RC2), XDS400.7 (!CS)
LCD_!INT: U400.9 (RC4), XDS400.8 (!INT)
LCD_!PD: U400.8 (RC3), XDS400.9 (!PD)
LCD_ADD_PIN: U400.2 (RA5), XDS400.10 (AUDIO_L)
LCD_BL_CTL: Q400.1 (G), U400.1 (RG15)
LCD_GND_BL: Q400.3 (D), XDS400.16 (GND_BL), XDS400.18 (GND_BL)
LCD_GPIO0: U400.6 (RC1), XDS400.11 (GPIO0/IO2)
LCD_GPIO1: U400.5 (RE7), XDS400.12 (GPIO1/IO3)
LCD_GPIO2: U400.4 (RE6), XDS400.13 (GPIO2)
LCD_GPIO3: U400.3 (RE5), XDS400.14 (GPIO3)
LCD_MISO: U400.11 (RG7), XDS400.5 (MISO/IO1)
LCD_MOSI: U400.12 (RG8), XDS400.6 (MOSI/IO0)
LCD_SCK: U400.10 (RG6), XDS400.4 (SCK)
LCD_V0: RV401.2 (S), XDS400.3 (NC1)
LCD_VBL: SJ401.2, XDS400.15 (VBL), XDS400.17 (VBL)
LED_B: J401.4, Q403.3 (D)
LED_G: J401.2, Q401.3 (D)
LED_R: J401.3, Q402.3 (D)
MCU_!MCLR: J400.1, R401.2, TP400.TP, U400.15 (!MCLR)
MCU_!MCLR!_FILT: C400.1, R400.1, R401.1, SW409.2
MCU_AUX_DETECT: J408.4, U400.73 (RC14)
MCU_BACK_SW: SW403.1, U400.97 (RG13)
MCU_BAT_SENSE: R411.2, U404.5 (+IN)
MCU_BAT_SENSE_BUF: C404.1, TP408.TP, U400.26 (RB6), U404.6 (-IN), U404.7 (OUT)
MCU_BAT_SENSE_FB: R411.1, U402.1 (OUT), U402.2 (-IN)
MCU_BAT_VDIV: R404.1, R405.2, U402.3 (+IN)
MCU_CURR_SENSE: R412.1, U404.3 (+IN)
MCU_CURR_SENSE_+: R409.1, R410.2, U402.5 (+IN)
MCU_CURR_SENSE_-: R407.2, R408.1, U402.6 (-IN)
MCU_CURR_SENSE_BUF: C403.1, TP409.TP, U400.27 (RB7), U404.1 (OUT), U404.2 (-IN)
MCU_CURR_SENSE_FB: R407.1, R412.2, U402.7 (OUT)
MCU_FWD_SW: SW405.1, U400.99 (RE3)
MCU_LCD_BL_SW: SW406.1, U400.100 (RE4)
MCU_LED_B: Q403.1 (G), U400.20 (RB5)
MCU_LED_G: Q401.1 (G), U400.18 (RE8)
MCU_LED_MODE1: SW407.1 (O), U400.16 (RG9)
MCU_LED_MODE2: SW407.3 (S), U400.17 (RA0)
MCU_LED_POT: RV400.2 (S), U400.21 (RB4)
MCU_LED_R: Q402.1 (G), U400.19 (RE9)
MCU_MFB_SW: SW401.1, U400.95 (RG14)
MCU_OSC1: C405.2, U400.49 (RC12), Y400.2
MCU_OSC2: R406.2, U400.50 (RC15)
MCU_OSC2_R: C406.2, R406.1, Y400.1
MCU_PGC: J400.5, U400.24 (RB1)
MCU_PGD: J400.4, U400.25 (RB0)
MCU_PLAY_SW: SW404.1, U400.98 (RE2)
MCU_SWLED_MAIN: Q404.1 (G), U400.22 (RB3)
MCU_SWLED_PWR: Q405.1 (G), U400.23 (RB2)
MCU_UART_RX: U400.81 (RD4), U403.5 (B1)
MCU_UART_TX: U400.82 (RD5), U403.2 (B1)
MCU_VOL+_SW: SW402.1, U400.96 (RG12)
MCU_VOL-_SW: SW400.1, U400.94 (RE1)
SWLED_MAIN: J402.2, Q404.3 (D)
SWLED_PWR: J402.3, Q405.3 (D)
VBAT: R404.2; also elsewhere on the board

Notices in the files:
firmware/src/config/default/peripheral/gpio/plib_gpio.h:
Copyright (C) 2019 Microchip Technology Inc. and its subsidiaries.
BlockBox v2.brd:
©2020 BlockWorker
